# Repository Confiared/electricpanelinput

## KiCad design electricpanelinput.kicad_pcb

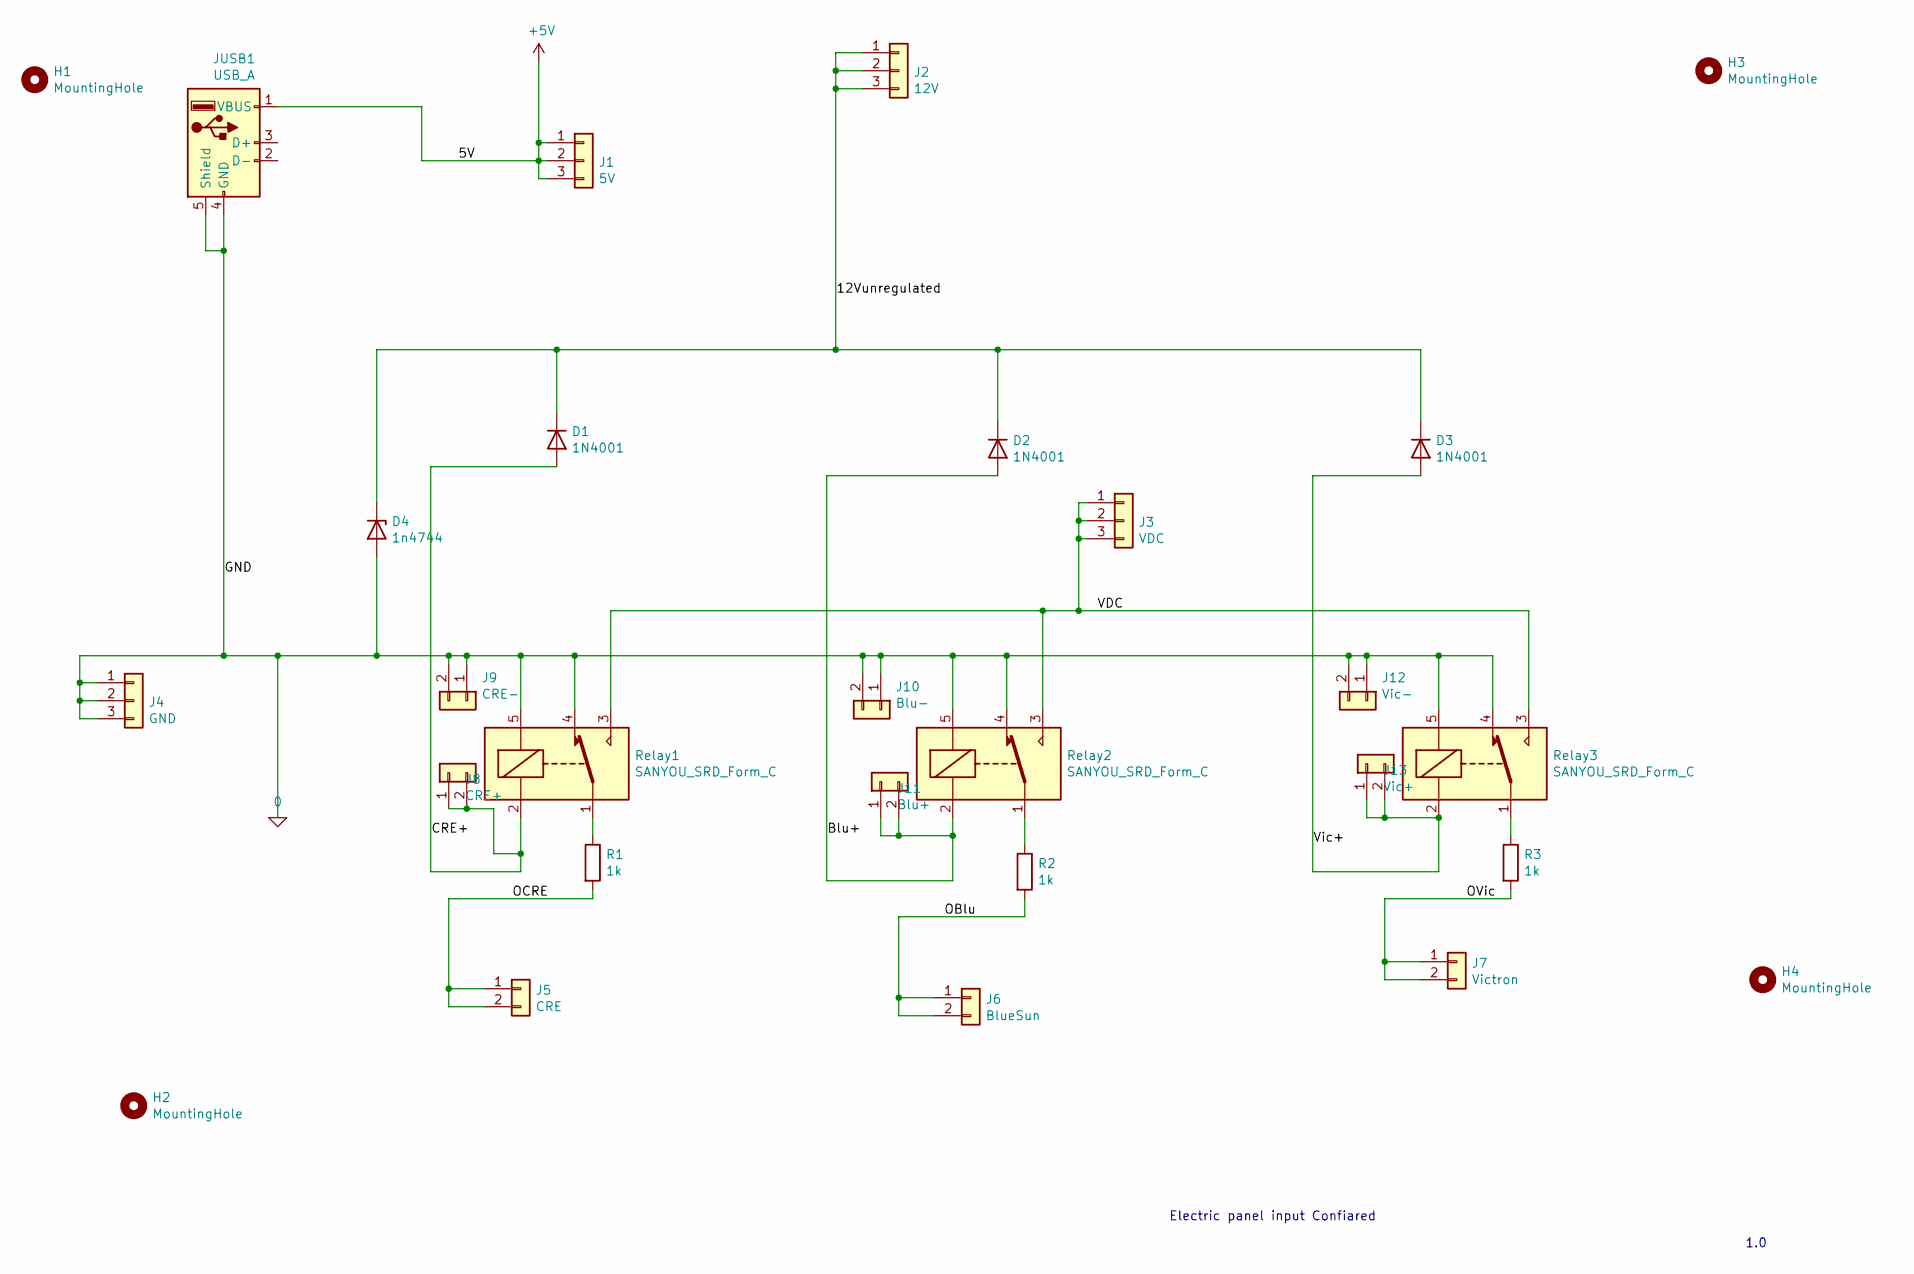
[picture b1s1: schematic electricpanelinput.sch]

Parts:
D1, D2, D3: 1N4001; D_DO-41_SOD81_P10.16mm_Horizontal
D4: 1n4744; D_DO-41_SOD81_P10.16mm_Horizontal
H1, H2, H3, H4: MountingHole; MountingHole_3.2mm_M3
J1: 5V; PinHeader_1x03_P2.54mm_Vertical
J2: 12V; PinHeader_1x03_P2.54mm_Vertical
J3: VDC; PinHeader_1x03_P2.54mm_Vertical
J4: GND; PinHeader_1x03_P2.54mm_Vertical
J5: CRE; PinHeader_1x02_P2.54mm_Vertical
J6: BlueSun; PinHeader_1x02_P2.54mm_Vertical
J7: Victron; PinHeader_1x02_P2.54mm_Vertical
J8: CRE+; PinHeader_1x02_P2.54mm_Vertical
J9: CRE-; PinHeader_1x02_P2.54mm_Vertical
J10: Blu-; PinHeader_1x02_P2.54mm_Vertical
J11: Blu+; PinHeader_1x02_P2.54mm_Vertical
J12: Vic-; PinHeader_1x02_P2.54mm_Vertical
J13: Vic+; PinHeader_1x02_P2.54mm_Vertical
JUSB1: USB_A; USB_A_Molex_67643_Horizontal
R1, R2, R3: 1k; R_Axial_DIN0207_L6.3mm_D2.5mm_P10.16mm_Horizontal
Relay1, Relay2, Relay3: SANYOU_SRD_Form_C; Relay_SPDT_SANYOU_SRD_Series_Form_C

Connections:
0: D4.2 (A), J4.1, J4.2, J4.3, J9.1, J9.2, J10.1, J10.2, J12.1, J12.2, JUSB1.4 (GND), JUSB1.5 (Shield), Relay1.4, Relay1.5, Relay2.4, Relay2.5, Relay3.4, Relay3.5
+5V: J1.1, J1.2, J1.3, JUSB1.1 (VBUS)
/12Vunregulated: D1.1 (K), D2.1 (K), D3.1 (K), D4.1 (K), J2.1, J2.2, J2.3
/Blu+: D2.2 (A), J11.1, J11.2, Relay2.2
/CRE+: D1.2 (A), J8.1, J8.2, Relay1.2
/OBlu: J6.1, J6.2, R2.2
/OCRE: J5.1, J5.2, R1.2
/OVic: J7.1, J7.2, R3.2
/VDC: J3.1, J3.2, J3.3, Relay1.3, Relay2.3, Relay3.3
/Vic+: D3.2 (A), J13.1, J13.2, Relay3.2
unnamed: R1.1, Relay1.1
unnamed: R2.1, Relay2.1
unnamed: R3.1, Relay3.1

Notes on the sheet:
Electric panel input Confiared
1.0

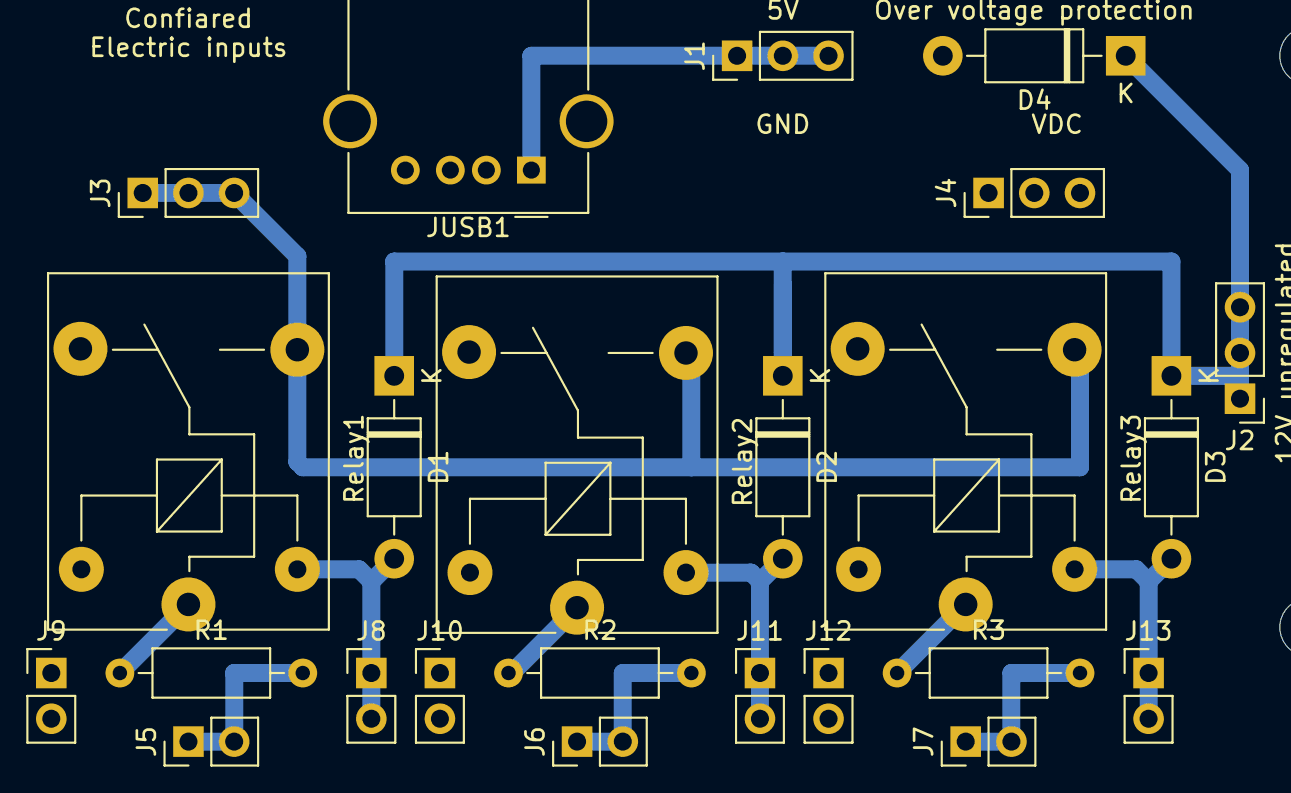
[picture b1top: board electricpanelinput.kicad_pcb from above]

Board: 2 copper layers, 28 parts (0 on the bottom side), 13 nets.

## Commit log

2020-08-14 Final work
2020-10-21 1 Layer PCB, input resistor protection
